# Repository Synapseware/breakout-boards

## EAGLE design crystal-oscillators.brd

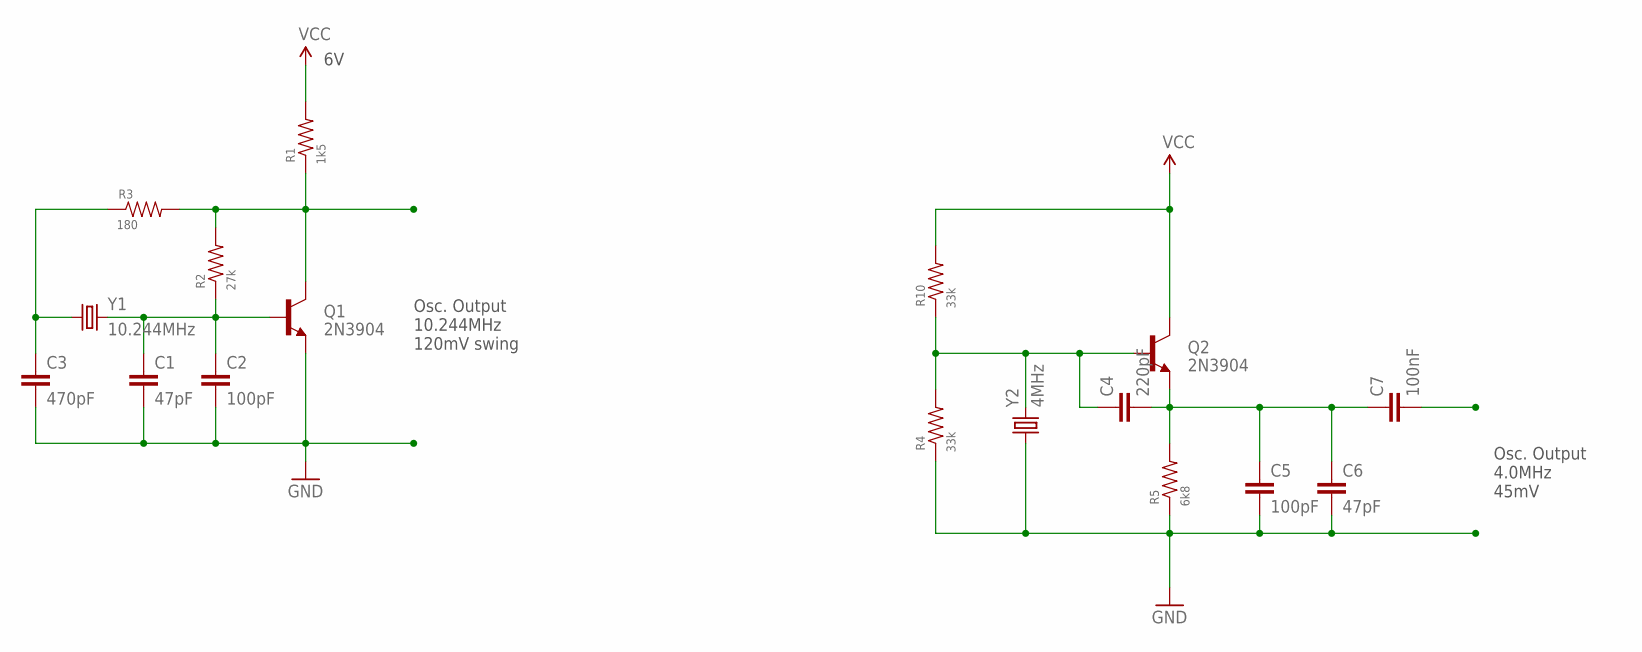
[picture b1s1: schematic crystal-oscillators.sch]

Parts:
C1, C6: 47pF; CAP-PTH-SMALL
C2, C5: 100pF; CAP-PTH-SMALL
C3: 470pF; CAP-PTH-SMALL
C4: 220pF; CAP-PTH-SMALL
C7: 100nF; CAP-PTH-SMALL
Q1, Q2: 2N3904; TO-92
R1: 1k5; VERT-PTH
R2: 27k; VERT-PTH
R3: 180; VERT-PTH
R4, R10: 33k; VERT-PTH
R5: 6k8; VERT-PTH
Y1: 10.244MHz; HC49US
Y2: 4MHz; HC49US

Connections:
GND: C1.2, C2.2, C3.2, C5.2, C6.2, Q1.3 (E), R4.1, R5.1, Y2.1
unnamed: C1.1, C2.1, Q1.2 (B), R2.1, Y1.2
unnamed: Q1.1 (C), R1.1, R2.2, R3.2
unnamed: C4.2, C5.1, C6.1, C7.1, Q2.3 (E), R5.2
unnamed: C4.1, Q2.2 (B), R4.2, R10.1, Y2.2
unnamed: C3.1, R3.1, Y1.1
VCC: Q2.1 (C), R1.2, R10.2

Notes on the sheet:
Osc. Output 10.244MHz 120mV swing
Osc. Output 4.0MHz 45mV

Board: 2 copper layers, 17 parts (0 on the bottom side), 7 nets, no tracks yet.

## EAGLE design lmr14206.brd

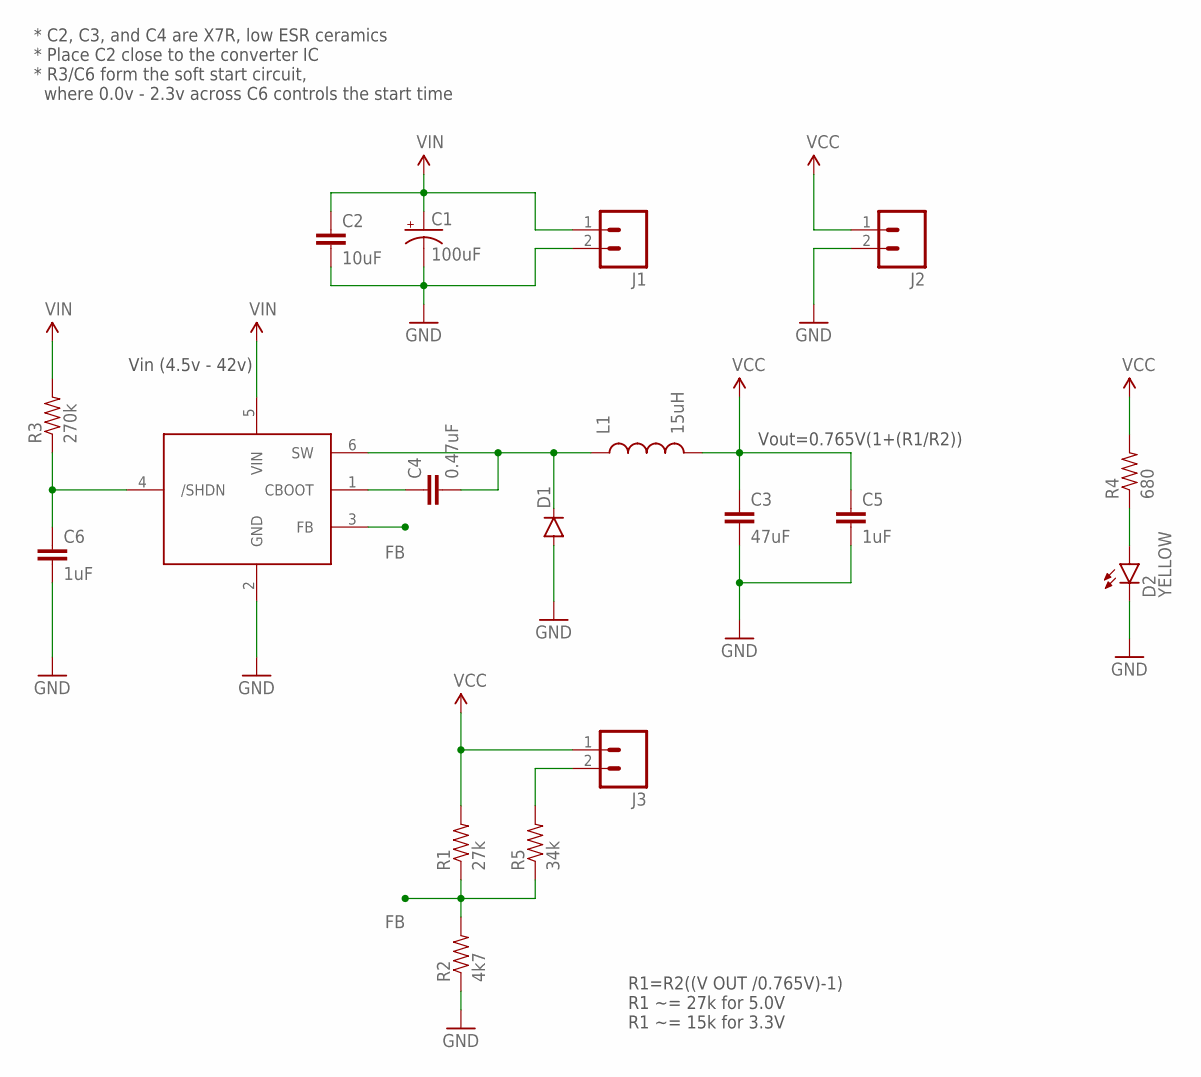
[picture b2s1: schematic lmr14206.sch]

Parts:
C1: 100uF; PANASONIC_C
C2: 10uF; 0805-CAP
C3: 47uF; 1210
C4: 0.47uF; 0805-CAP
C5, C6: 1uF; 0805-CAP
D1: DIODESMB; SMB-DIODE
D2: YELLOW; LED-1206
J1: M02JST-PTH-VERT; JST-2-PTH-VERT
J2, J3: M02PTH; 1X02
L1: 15uH; INDUCTOR-1206
R1: 27k; 0805
R2: 4k7; 0805
R3: 270k; 0805
R4: 680; 0805
R5: 34k; 0805
U$1: LMR14206TSOT-6; TSOT-6

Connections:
FB: R1.1, R2.2, R5.1, U$1.3 (FB)
GND: C1.-, C2.2, C3.2, C5.2, C6.2, D1.A, D2.C, J1.2, J2.2, R2.1, U$1.2 (GND)
unnamed: J3.2, R5.2
unnamed: D2.A, R4.1
unnamed: C4.1, U$1.1 (CBOOT)
unnamed: C4.2, D1.C, L1.P$1 (1), U$1.6 (SW)
unnamed: C6.1, R3.1, U$1.4 (/SHDN)
VCC: C3.1, C5.1, J2.1, J3.1, L1.P$2 (2), R1.2, R4.2
VIN: C1.+, C2.1, J1.1, R3.2, U$1.5 (VIN)

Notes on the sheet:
Vin (4.5v - 42v)
* C2, C3, and C4 are X7R, low ESR ceramics * Place C2 close to the converter IC * R3/C6 form the soft start circuit, where 0.0v - 2.3v across C6 controls the start time
Vout=0.765V(1+(R1/R2))
R1=R2((V OUT /0.765V)-1) R1 ~= 27k for 5.0V R1 ~= 15k for 3.3V

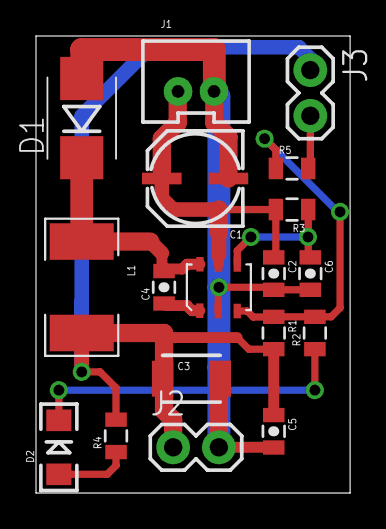
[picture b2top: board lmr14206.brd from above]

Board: 2 copper layers, 17.4 x 25.4 mm, 18 parts (0 on the bottom side), 9 nets.

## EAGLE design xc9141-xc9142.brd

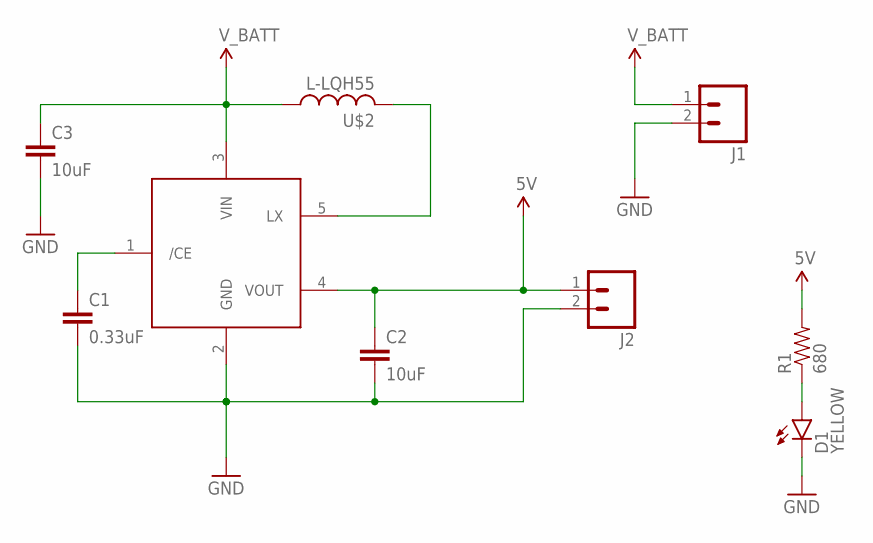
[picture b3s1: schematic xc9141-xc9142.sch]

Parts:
C1: 0.33uF; 0805-CAP
C2, C3: 10uF; 1206
D1: YELLOW; LED-1206
J1: M02JST-PTH-VERT; JST-2-PTH-VERT
J2: M02PTH3; 1X02_LONGPADS
R1: 680; 0805
U$1: XC9141/XC9142SOT-25; SOT-25
U$2: L-LQH55; LQH55

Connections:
5V: C2.1, J2.1, R1.2, U$1.4 (VOUT)
GND: C1.2, C2.2, C3.2, D1.C, J1.2, J2.2, U$1.2 (GND)
unnamed: D1.A, R1.1
unnamed: C1.1, U$1.1 (/CE)
unnamed: U$1.5 (LX), U$2.2
V_BATT: C3.1, J1.1, U$1.3 (VIN), U$2.1

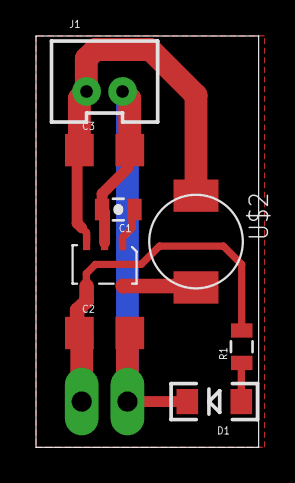
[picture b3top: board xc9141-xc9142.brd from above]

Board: 2 copper layers, 12.4 x 22.9 mm, 9 parts (0 on the bottom side), 6 nets.

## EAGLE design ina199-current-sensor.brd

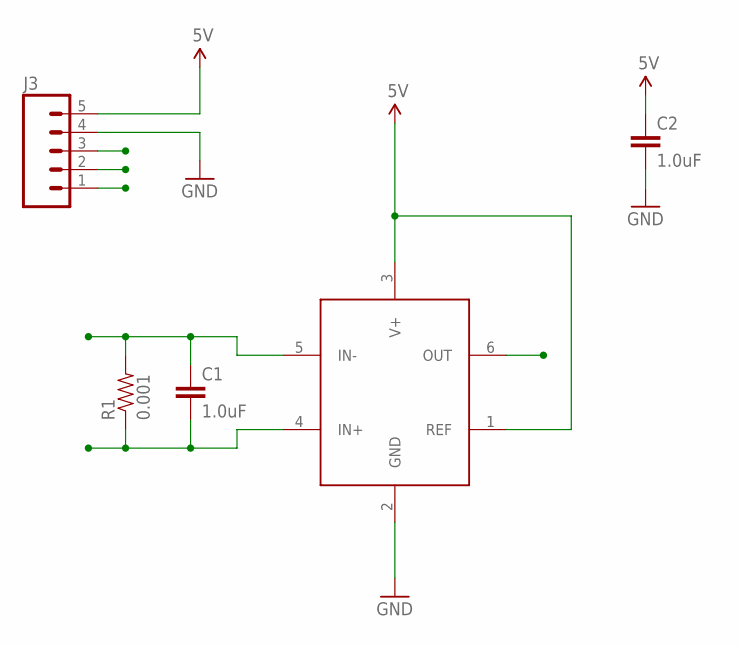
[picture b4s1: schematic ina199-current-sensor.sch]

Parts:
C1, C2: 1.0uF; 1206-CAP
J3: M05LOCK_LONGPADS; 1X05_LOCK_LONGPADS
R1: 0.001; 2512
U$1: INA199SC70; SC70-6

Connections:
5V: C2.1, J3.5, U$1.1 (REF), U$1.3 (V+)
GND: C2.2, J3.4, U$1.2 (GND)
LOAD: C1.1, J3.2, R1.2, U$1.5 (IN-)
OUT: J3.3, U$1.6 (OUT)
SUPPLY: C1.2, J3.1, R1.1, U$1.4 (IN+)

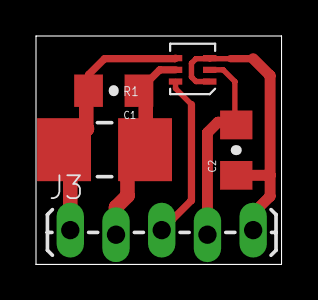
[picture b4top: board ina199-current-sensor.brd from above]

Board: 2 copper layers, 13.6 x 12.7 mm, 5 parts (0 on the bottom side), 5 nets.

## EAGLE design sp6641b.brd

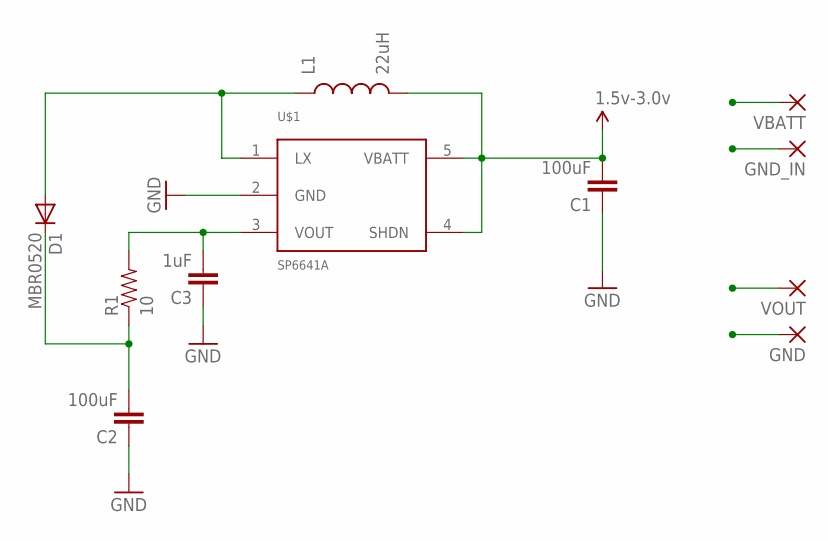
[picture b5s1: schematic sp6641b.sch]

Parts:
C1, C2: 100uF; 0805
C3: 1uF; 0805
D1: MBR0520; SOD123
GND: WIREPAD2,54/1,0; 2,54/1,0
GND_IN: WIREPAD2,54/1,0; 2,54/1,0
L1: 22uH; CR54
R1: 10; 0805
U$1: SP6641A; SOT23-5
VBATT: WIREPAD2,54/1,0; 2,54/1,0
VOUT: WIREPAD2,54/1,0; 2,54/1,0

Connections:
GND: C1.1, C2.1, C3.1, GND.1, GND_IN.1, U$1.2 (GND)
unnamed: C3.2, R1.2, U$1.3 (VOUT)
unnamed: D1.A, L1.P$1 (1), U$1.1 (LX)
VBATT: C1.2, L1.P$2 (2), U$1.4 (SHDN), U$1.5 (VBATT), VBATT.1
VOUT: C2.2, D1.C, R1.1, VOUT.1

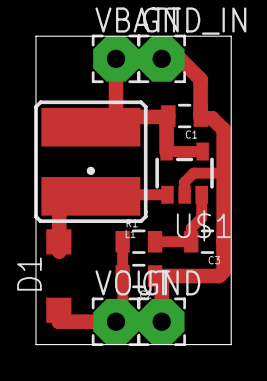
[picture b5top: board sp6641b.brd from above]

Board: 2 copper layers, 10.8 x 17.1 mm, 11 parts (0 on the bottom side), 5 nets.

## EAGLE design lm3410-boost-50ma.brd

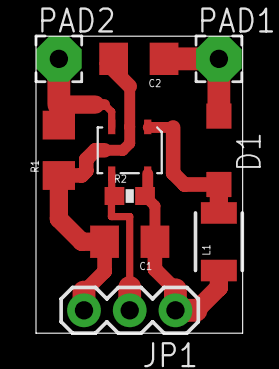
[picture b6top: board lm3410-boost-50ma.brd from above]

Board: 2 copper layers, 11.5 x 16.5 mm, 10 parts (0 on the bottom side), 6 nets.

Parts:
C1: 10uF/6.3v; 1206
C2: 2.2uF/25v; 1206
D1: MBR0530; SOD123
JP1: 1X03
L1: 10uH/1.2A; 1210
PAD1, PAD2: 2,54/1,0
R1: 4; 1206
R2: 100k; 0603-RES
U$1: LM3410-SOT-23-5; SOT-23-5

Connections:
DIM: JP1.2, R2.1, U$1.4
GND: C1.2, C2.2, JP1.3, R1.1, U$1.2
unnamed: D1.A, L1.2, U$1.1
unnamed: PAD2.1, R1.2, U$1.3
unnamed: C2.1, D1.C, PAD1.1
VCC: C1.1, JP1.1, L1.1, R2.2, U$1.5

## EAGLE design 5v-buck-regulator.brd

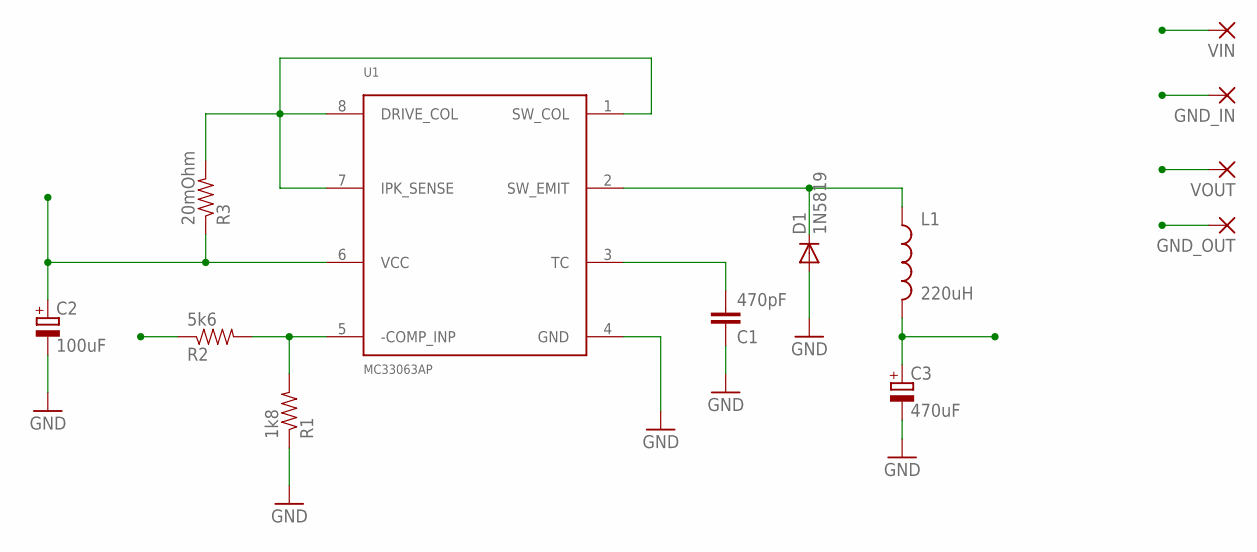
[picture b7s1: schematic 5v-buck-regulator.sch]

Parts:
C1: 470pF; 0805
C2: 100uF; PANASONIC_C
C3: 470uF; PANASONIC_D
D1: 1N5819; SOD123
GND_IN: WIREPAD2,54/0,8; 2,54/0,8
GND_OUT: WIREPAD2,54/0,8; 2,54/0,8
L1: 220uH; B82462G
R1: 1k8; 0805
R2: 5k6; 0805
R3: 20mOhm; R2010
U1: MC33063AP; SOIC-8
VIN: WIREPAD2,54/0,8; 2,54/0,8
VOUT: WIREPAD2,54/0,8; 2,54/0,8

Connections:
GND: C1.1, C2.-, C3.-, D1.A, GND_IN.1, GND_OUT.1, R1.1, U1.4 (GND)
unnamed: C1.2, U1.3 (TC)
unnamed: R3.2, U1.1 (SW_COL), U1.7 (IPK_SENSE), U1.8 (DRIVE_COL)
unnamed: D1.C, L1.P$1 (1), U1.2 (SW_EMIT)
unnamed: R1.2, R2.2, U1.5 (-COMP_INP)
VIN: C2.+, R3.1, U1.6 (VCC), VIN.1
VOUT: C3.+, L1.P$2 (2), R2.1, VOUT.1

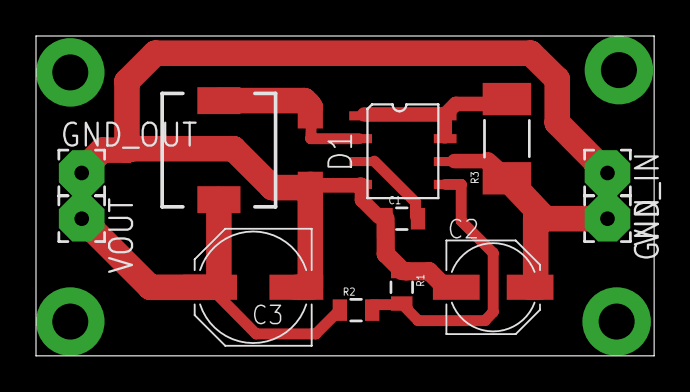
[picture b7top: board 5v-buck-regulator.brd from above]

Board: 2 copper layers, 34.3 x 17.8 mm, 13 parts (0 on the bottom side), 7 nets.

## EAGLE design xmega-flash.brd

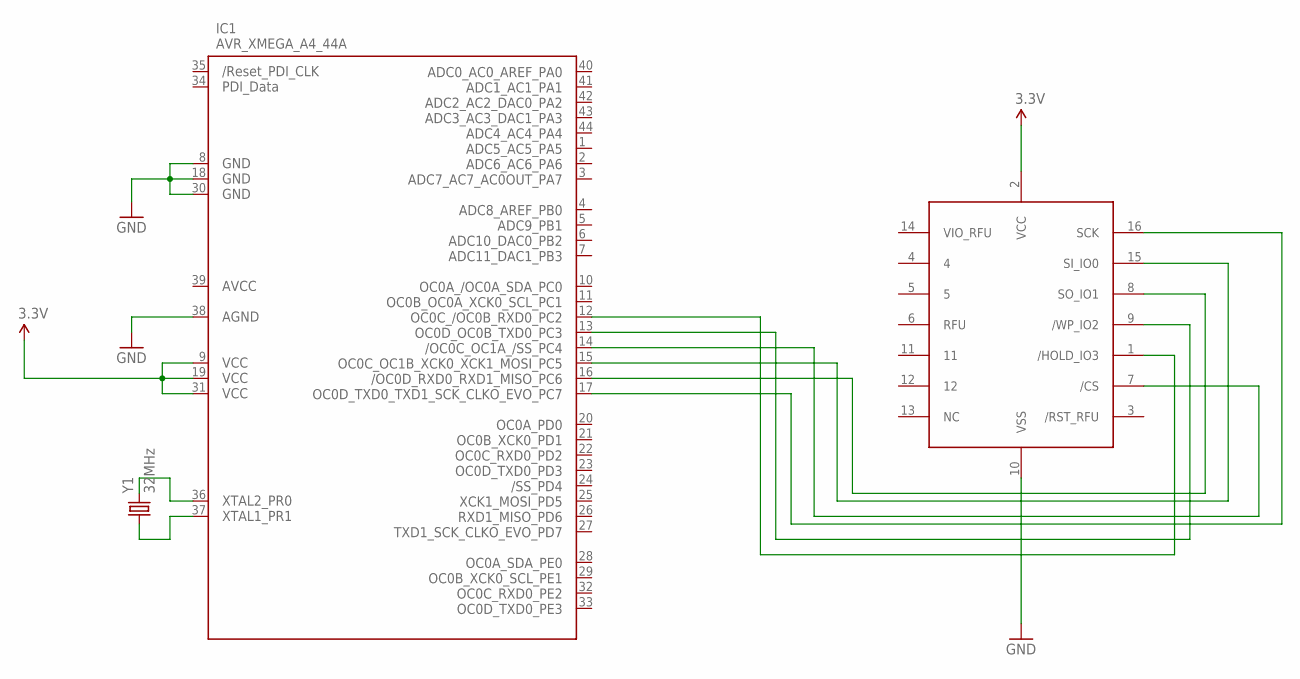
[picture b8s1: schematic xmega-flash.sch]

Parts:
IC1: AVR_XMEGA_A4_44A; TQFP44
U$1: S25FLS256; WSOIC-16
Y1: 32MHz; CRYSTAL-SMD-5X3

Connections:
3.3V: IC1.9 (VCC1), IC1.19 (VCC2), IC1.31 (VCC3), U$1.2 (VCC)
GND: IC1.8 (GND1), IC1.18 (GND2), IC1.30 (GND3), IC1.38 (AGND), U$1.10 (VSS)
unnamed: IC1.17 (PC7), U$1.16 (SCK)
unnamed: IC1.14 (PC4), U$1.7 (/CS)
unnamed: IC1.15 (PC5), U$1.15 (SI_IO0)
unnamed: IC1.16 (PC6), U$1.8 (SO_IO1)
unnamed: IC1.13 (PC3), U$1.9 (/WP_IO2)
unnamed: IC1.12 (PC2), U$1.1 (/HOLD_IO3)
unnamed: IC1.36 (PR0), Y1.3 (2)
unnamed: IC1.37 (PR1), Y1.1

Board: 2 copper layers, 3 parts (0 on the bottom side), 10 nets, no tracks yet.

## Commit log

2014-06-03 Adding lm3405 breakout board
2014-07-29 Updating layout for lm3410 breakout board
2017-02-26 Adding Sp6641B breakout board
2017-08-18 Modified board layouts
2017-12-27 Ignore EPF files
2019-09-10 Adding XC9142 breakout board
2019-09-16 Breakout board updates
2019-09-17 A couple of different osc.

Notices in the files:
parts and their libraries:
SparkFun: Licensing: CC v3.0 Share-Alike You are welcome to use this library for commercial purposes.
SparkFun-Capacitors: Licensing: Creative Commons ShareAlike 4.0 International - https://creativecommons.org/licenses/by-sa/4.0
